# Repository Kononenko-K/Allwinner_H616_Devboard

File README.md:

# Allwinner_H616_Devboard
A minimalistic development board designed for the Cortex-A53 Allwinner H616 SoC using KiCad

## Overview
The goal of this project, based on the schematics of Orange Pi Zero 2 and Orange Pi Zero 3, was to create a minimalistic development board for the H616 SoC with a functional DDR3/LPDDR4 topology and power supply. This allows it to be used as a basic design that can be modified for specific applications.

## [Hardware](Hardware)
Both versions of the board are powered by the 64-bit 1.5GHz Quad-Core Cortex-A53 Allwinner H616 SoC, supporting either Allwinner H616 or its pin-to-pin compatible successor, Allwinner H618. The primary difference between these chips is the increased L2 cache size in the H618 model.
#### [DDR3 Version:](/Hardware/H616_DDR3)

The DDR3 variant features a compact design optimized for simplicity and ease of learning. Key components include:

- **Memory:** Up to 8 Gbit (1 GB) of BGA-96 16x DDR3 RAM
- **Power Management:** X-Powers AXP305 PMIC
- **Connectivity:** Micro SD slot, USB HS Host connector
- **Communication:** Integrated CP2102 USB-UART converter

#### [LPDDR4 Version:](/Hardware/H616_LPDDR4)

The LPDDR4 variant offers enhanced capabilities tailored for my specific application, while also remaining suitable for educational use:

- **Memory:** Up to 32 Gbit (4 GB) of BGA-200 32x LPDDR4 RAM
- **Power Management:** X-Powers AXP313A PMIC
- **Storage:** Integrated SD2.0 Flash Memory chip and MicroSD slot for flexible storage options
- **Auxiliary Processing:** Cortex-M4 STM32 microcontroller for additional processing tasks
- **Communication:** Integrated CP2102 USB-UART converter

To power the board via USB and connect external devices, a custom [USB board adapter](/Hardware/Debug_Adapter) is available.

### **Manufacturing specifications:**
- **Layers:** 4-layer design  
- **Trace/Space:** 3.5/3.5 mil  
- **Via Sizes:** 0.35/0.15 mm 
- **Prepreg:** 80u  

There are PDF documents available for both [DDR3](/Hardware/H616_DDR3/project.pdf) and [LPDDR4](/Hardware/H616_LPDDR4/project.pdf) versions.

## Software

### **Building from Mainline:**
#### Arm Trusted Firmware (TF-A):
- Source: [here](https://git.trustedfirmware.org/TF-A/trusted-firmware-a.git/)
```sh
make CROSS_COMPILE=aarch64-linux-gnu- PLAT=sun50i_h616 RESET_TO_BL31=1
```
After building, copy the `bl31.bin` file to the U-Boot sources directory.

#### U-Boot:
- Source: [here](https://github.com/u-boot/u-boot)
```sh
make ARCH=arm CROSS_COMPILE=aarch64-linux-gnu- orangepi_zero2_defconfig
make ARCH=arm CROSS_COMPILE=aarch64-linux-gnu- BL31=bl31.bin
```

#### Linux Kernel:
- Source: [www.kernel.org](http://www.kernel.org)
```sh
make ARCH=arm64 CROSS_COMPILE=aarch64-linux-gnu- defconfig
make ARCH=arm64 CROSS_COMPILE=aarch64-linux-gnu- Image modules dtbs
```

#### Rootfs:
Example sources for arm64 rootfs:
- [rcn-ee.com](https://rcn-ee.com/rootfs/eewiki/minfs)
- [Linaro.org](https://releases.linaro.org/openembedded/images/)

#### Preparing SD Card:
1. Create two partitions: a small fat32 for boot files and an ext4 for rootfs.
2. Write U-Boot to the card:
```sh
sudo dd if=/dev/zero of=/dev/mmcblk0 bs=1k count=1023 seek=1
sudo dd if=u-boot-sunxi-with-spl.bin of=/dev/mmcblk0 bs=1024 seek=8
```
3. Copy dtb and kernel image to the first partition, then unpack rootfs to the second.

If you prefer to load U-Boot into RAM and execute it directly over USB without using an SD card, you can use the `sunxi-fel` utility:  
   ```sh
   sudo sunxi-fel uboot u-boot-sunxi-with-spl.bin
   ```  
This method is useful for testing or when bypassing the SD card for some reason.

#### Booting from U-Boot:
Enter these commands in the U-Boot console:
```sh
setenv bootargs console=ttyS0,115200 root=/dev/mmcblk0p2 rw rootwait
setenv bootcmd "mmc rescan; fatload mmc 0:1 0x46000000 Image; fatload mmc 0:1 0x49000000 sun50i-h616-orangepi-zero2.dtb; booti 0x46000000 - 0x49000000"
```
Use a `boot.scr` file for automatic booting.

### **Using Buildroot:**
For LPDDR4 version:
```sh
make orangepi_zero3_defconfig
```
For DDR3 versions, modify the config:
```sh
BR2_LINUX_KERNEL_INTREE_DTS_NAME="allwinner/sun50i-h616-orangepi-zero2.dts"
BR2_TARGET_UBOOT_BOARD_DEFCONFIG="orangepi_zero2"
```
Download sources with `make source`, then build.

## License
- The **Hardware** in this project is licensed under the [CERN Open Hardware Licence Permissive (CERN OHL-P)](LICENSE).

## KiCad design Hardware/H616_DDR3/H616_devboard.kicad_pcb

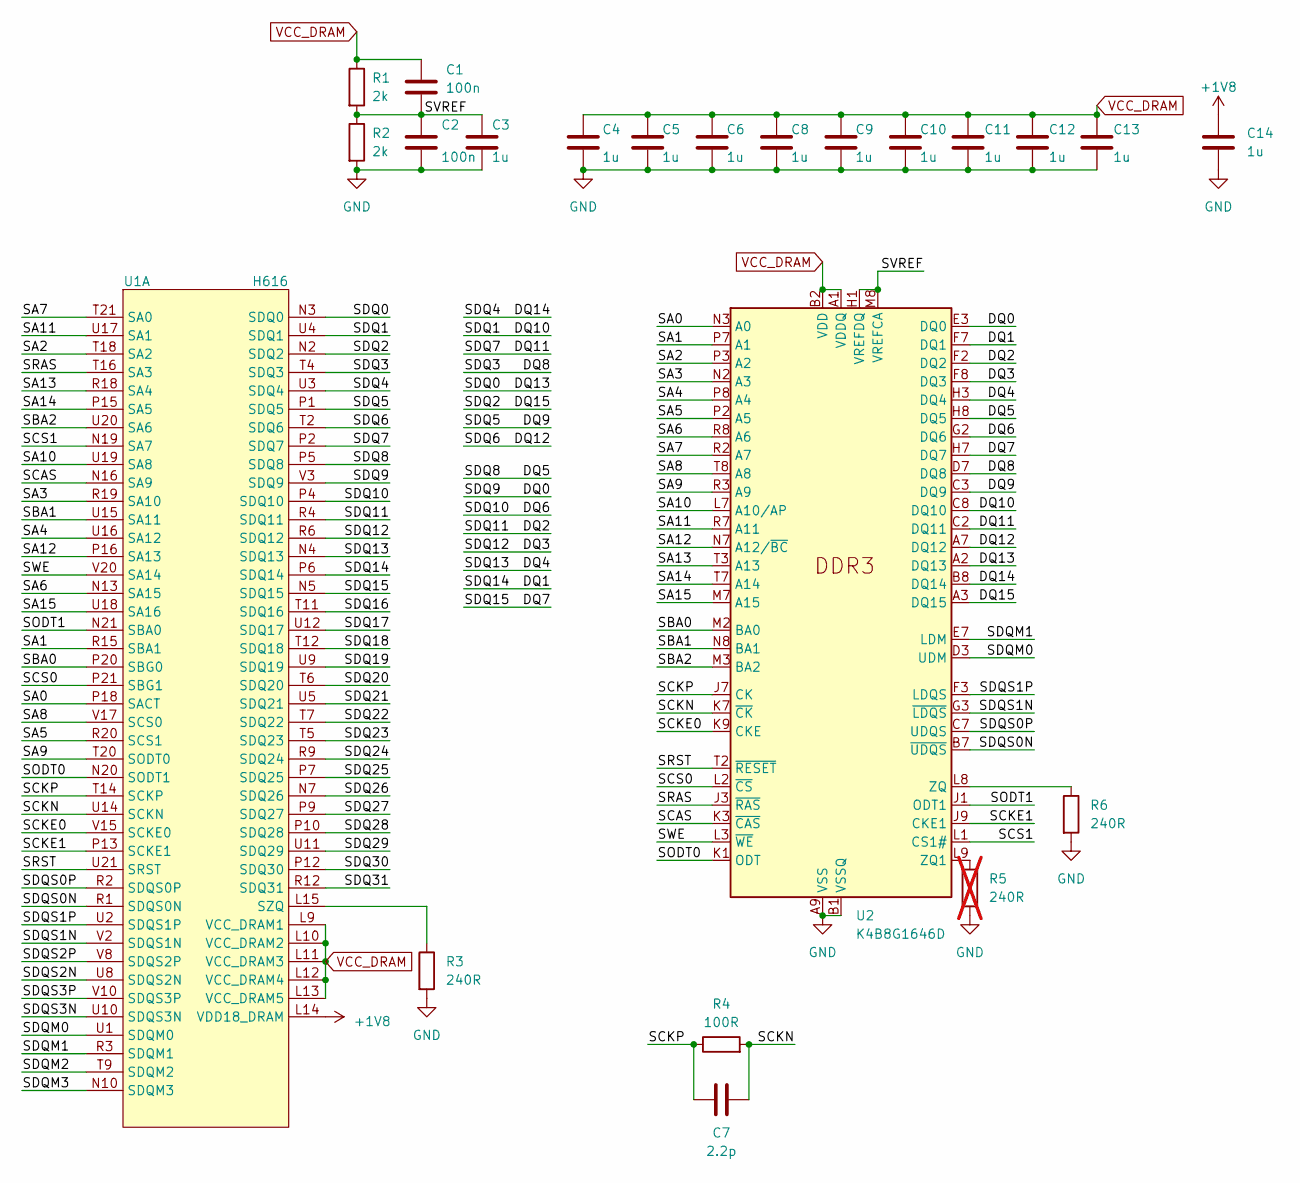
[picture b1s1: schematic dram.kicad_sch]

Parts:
C1, C2: 100n; C_0402_1005Metric_Pad0.74x0.62mm_HandSolder
C3, C4, C5, C6, C8, C9, C10, C11, C12, C13, C14: 1u; C_0402_1005Metric_Pad0.74x0.62mm_HandSolder
C7: 2.2p; C_0402_1005Metric_Pad0.74x0.62mm_HandSolder
R1, R2: 2k; R_0402_1005Metric_Pad0.72x0.64mm_HandSolder
R3, R6: 240R; R_0402_1005Metric_Pad0.72x0.64mm_HandSolder
R4: 100R; R_0402_1005Metric_Pad0.72x0.64mm_HandSolder
R5: 240R; R_0402_1005Metric_Pad0.72x0.64mm_HandSolder; not fitted
U1: H616; H616_TFBGA284
U2: K4B8G1646D; BGA-96_9.0x13.0mm_Layout2x3x16_P0.8mm

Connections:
+1V8: C14.1, U1.L14 (VDD18_DRAM); also elsewhere on the board
/DRAM/DQ0: U1.V3 (SDQ9), U2.E3 (DQ0)
/DRAM/DQ1: U1.P6 (SDQ14), U2.F7 (DQ1)
/DRAM/DQ2: U1.R4 (SDQ11), U2.F2 (DQ2)
/DRAM/DQ3: U1.R6 (SDQ12), U2.F8 (DQ3)
/DRAM/DQ4: U1.N4 (SDQ13), U2.H3 (DQ4)
/DRAM/DQ5: U1.P5 (SDQ8), U2.H8 (DQ5)
/DRAM/DQ6: U1.P4 (SDQ10), U2.G2 (DQ6)
/DRAM/DQ7: U1.N5 (SDQ15), U2.H7 (DQ7)
/DRAM/DQ8: U1.T4 (SDQ3), U2.D7 (DQ8)
/DRAM/DQ9: U1.P1 (SDQ5), U2.C3 (DQ9)
/DRAM/DQ10: U1.U4 (SDQ1), U2.C8 (DQ10)
/DRAM/DQ11: U1.P2 (SDQ7), U2.C2 (DQ11)
/DRAM/DQ12: U1.T2 (SDQ6), U2.A7 (DQ12)
/DRAM/DQ13: U1.N3 (SDQ0), U2.A2 (DQ13)
/DRAM/DQ14: U1.U3 (SDQ4), U2.B8 (DQ14)
/DRAM/DQ15: U1.N2 (SDQ2), U2.A3 (DQ15)
/DRAM/SA0: U1.P18 (SACT), U2.N3 (A0)
/DRAM/SA1: U1.R15 (SBA1), U2.P7 (A1)
/DRAM/SA2: U1.T18 (SA2), U2.P3 (A2)
/DRAM/SA3: U1.R19 (SA10), U2.N2 (A3)
/DRAM/SA4: U1.U16 (SA12), U2.P8 (A4)
/DRAM/SA5: U1.R20 (SCS1), U2.P2 (A5)
/DRAM/SA6: U1.N13 (SA15), U2.R8 (A6)
/DRAM/SA7: U1.T21 (SA0), U2.R2 (A7)
/DRAM/SA8: U1.V17 (SCS0), U2.T8 (A8)
/DRAM/SA9: U1.T20 (SODT0), U2.R3 (A9)
/DRAM/SA10: U1.U19 (SA8), U2.L7 (A10/AP)
/DRAM/SA11: U1.U17 (SA1), U2.R7 (A11)
/DRAM/SA12: U1.P16 (SA13), U2.N7 (A12/~BC)
/DRAM/SA13: U1.R18 (SA4), U2.T3 (A13)
/DRAM/SA14: U1.P15 (SA5), U2.T7 (A14)
/DRAM/SA15: U1.U18 (SA16), U2.M7 (A15)
/DRAM/SBA0: U1.P20 (SBG0), U2.M2 (BA0)
/DRAM/SBA1: U1.U15 (SA11), U2.N8 (BA1)
/DRAM/SBA2: U1.U20 (SA6), U2.M3 (BA2)
/DRAM/SCAS: U1.N16 (SA9), U2.K3 (~CAS)
/DRAM/SCKE0: U1.V15 (SCKE0), U2.K9 (CKE)
/DRAM/SCKE1: U1.P13 (SCKE1), U2.J9 (CKE1)
/DRAM/SCKN: C7.2, R4.2, U1.U14 (SCKN), U2.K7 (~CK)
/DRAM/SCKP: C7.1, R4.1, U1.T14 (SCKP), U2.J7 (CK)
/DRAM/SCS0: U1.P21 (SBG1), U2.L2 (~CS)
/DRAM/SCS1: U1.N19 (SA7), U2.L1 (CS1#)
/DRAM/SDQ16: U1.T11 (SDQ16)
/DRAM/SDQ17: U1.U12 (SDQ17)
/DRAM/SDQ18: U1.T12 (SDQ18)
/DRAM/SDQ19: U1.U9 (SDQ19)
/DRAM/SDQ20: U1.T6 (SDQ20)
/DRAM/SDQ21: U1.U5 (SDQ21)
/DRAM/SDQ22: U1.T7 (SDQ22)
/DRAM/SDQ23: U1.T5 (SDQ23)
/DRAM/SDQ24: U1.R9 (SDQ24)
/DRAM/SDQ25: U1.P7 (SDQ25)
/DRAM/SDQ26: U1.N7 (SDQ26)
/DRAM/SDQ27: U1.P9 (SDQ27)
/DRAM/SDQ28: U1.P10 (SDQ28)
/DRAM/SDQ29: U1.U11 (SDQ29)
/DRAM/SDQ30: U1.P12 (SDQ30)
/DRAM/SDQ31: U1.R12 (SDQ31)
/DRAM/SDQM0: U1.U1 (SDQM0), U2.D3 (UDM)
/DRAM/SDQM1: U1.R3 (SDQM1), U2.E7 (LDM)
/DRAM/SDQM2: U1.T9 (SDQM2)
/DRAM/SDQM3: U1.N10 (SDQM3)
/DRAM/SDQS0N: U1.R1 (SDQS0N), U2.B7 (~UDQS)
/DRAM/SDQS0P: U1.R2 (SDQS0P), U2.C7 (UDQS)
/DRAM/SDQS1N: U1.V2 (SDQS1N), U2.G3 (~LDQS)
/DRAM/SDQS1P: U1.U2 (SDQS1P), U2.F3 (LDQS)
/DRAM/SDQS2N: U1.U8 (SDQS2N)
/DRAM/SDQS2P: U1.V8 (SDQS2P)
/DRAM/SDQS3N: U1.U10 (SDQS3N)
/DRAM/SDQS3P: U1.V10 (SDQS3P)
/DRAM/SODT0: U1.N20 (SODT1), U2.K1 (ODT)
/DRAM/SODT1: U1.N21 (SBA0), U2.J1 (ODT1)
/DRAM/SRAS: U1.T16 (SA3), U2.J3 (~RAS)
/DRAM/SRST: U1.U21 (SRST), U2.T2 (~RESET)
/DRAM/SVREF: C1.2, C2.1, C3.1, R1.2, R2.1, U2.H1 (VREFDQ), U2.M8 (VREFCA)
/DRAM/SWE: U1.V20 (SA14), U2.L3 (~WE)
GND: C2.2, C3.2, C4.2, C5.2, C6.2, C8.2, C9.2, C10.2, C11.2, C12.2, C13.2, C14.2, R2.2, R3.2, R5.2, R6.2, U2.A9 (VSS), U2.B1 (VSSQ), U2.B3 (VSS), U2.B9 (VSSQ), U2.D1 (VSSQ), U2.D8 (VSSQ), U2.E1 (VSS), U2.E2 (VSSQ), U2.E8 (VSSQ), U2.F9 (VSSQ), U2.G1 (VSSQ), U2.G8 (VSS), U2.G9 (VSSQ), U2.J2 (VSS), U2.J8 (VSS), U2.M1 (VSS), U2.M9 (VSS), U2.P1 (VSS), U2.P9 (VSS), U2.T1 (VSS), U2.T9 (VSS); also elsewhere on the board
unnamed: R3.1, U1.L15 (SZQ)
unnamed: R5.1, U2.L9 (ZQ1)
unnamed: R6.1, U2.L8 (ZQ)
VCC_DRAM: C1.1, C4.1, C5.1, C6.1, C8.1, C9.1, C10.1, C11.1, C12.1, C13.1, R1.1, U1.L9 (VCC_DRAM1), U1.L10 (VCC_DRAM2), U1.L11 (VCC_DRAM3), U1.L12 (VCC_DRAM4), U1.L13 (VCC_DRAM5), U2.A1 (VDDQ), U2.A8 (VDDQ), U2.B2 (VDD), U2.C1 (VDDQ), U2.C9 (VDDQ), U2.D2 (VDDQ), U2.D9 (VDD), U2.E9 (VDDQ), U2.F1 (VDDQ), U2.G7 (VDD), U2.H2 (VDDQ), U2.H9 (VDDQ), U2.K2 (VDD), U2.K8 (VDD), U2.N1 (VDD), U2.N9 (VDD), U2.R1 (VDD), U2.R9 (VDD); also elsewhere on the board

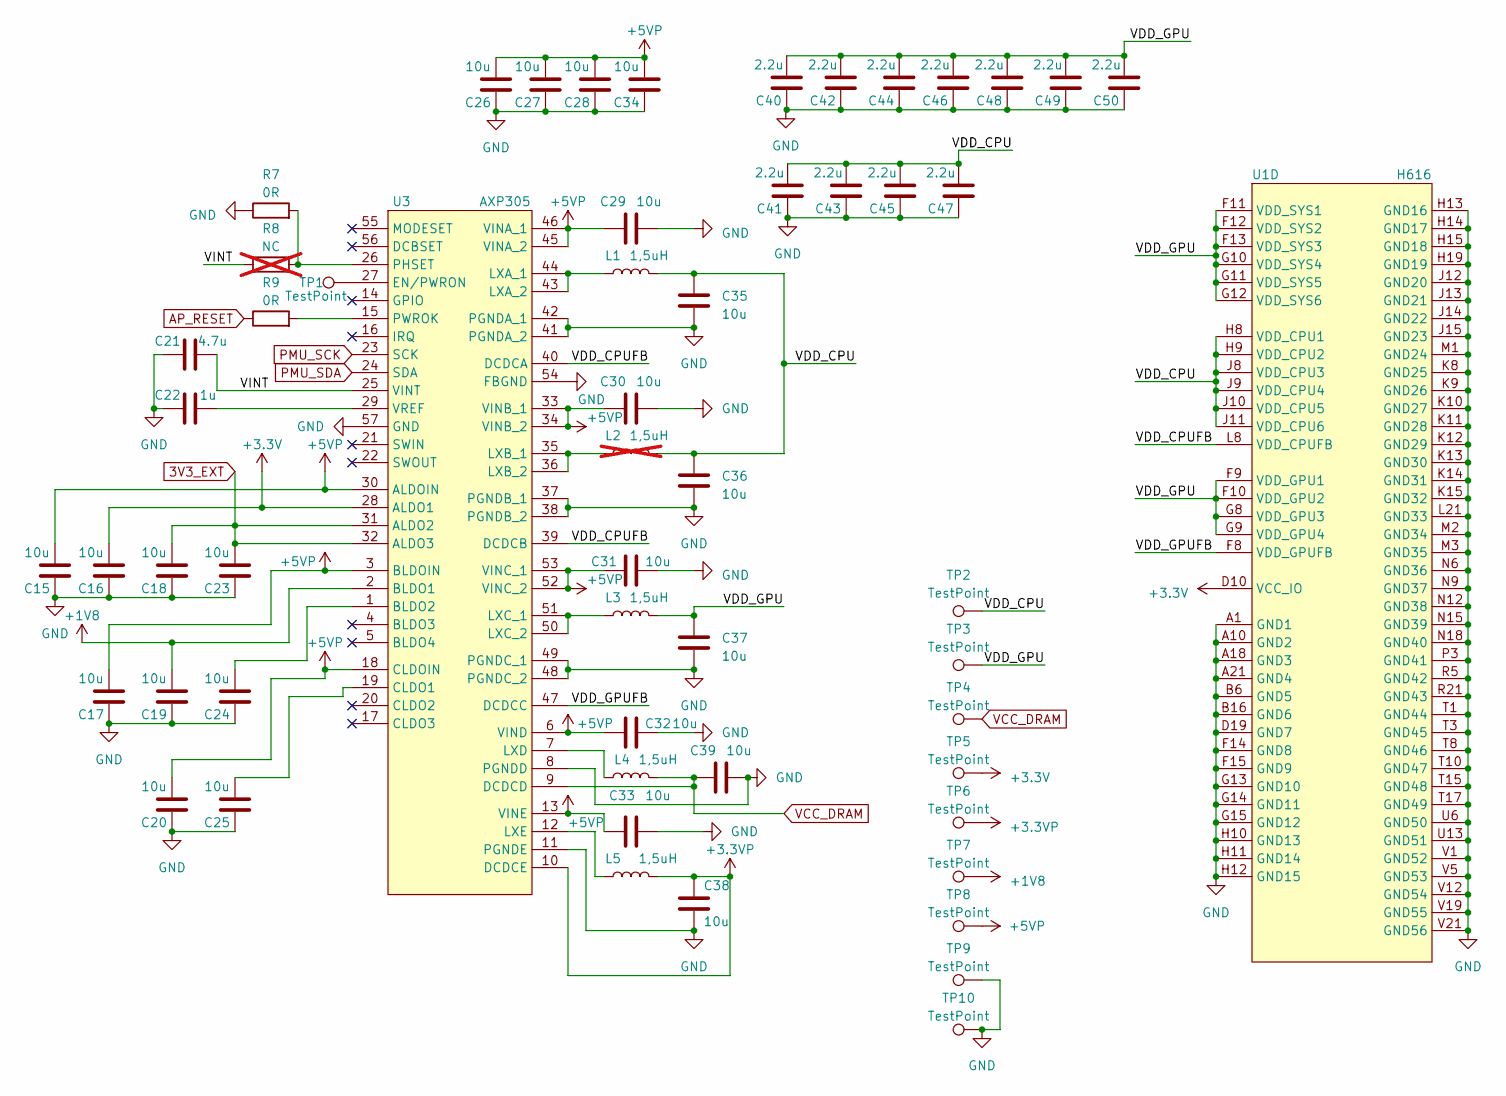
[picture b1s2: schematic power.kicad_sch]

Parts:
C15, C16, C17, C18, C19, C20, C23, C24, C25, C26, C27, C28, C29, C30, C31, C32, C33, C34, C35, C36, C37, C38, C39: 10u; C_0402_1005Metric_Pad0.74x0.62mm_HandSolder
C21: 4.7u; C_0402_1005Metric_Pad0.74x0.62mm_HandSolder
C22: 1u; C_0402_1005Metric_Pad0.74x0.62mm_HandSolder
C40, C41, C42, C43, C44, C45, C46, C47, C48, C49, C50: 2.2u; C_0402_1005Metric_Pad0.74x0.62mm_HandSolder
L1, L3, L4, L5: 1,5uH; L_Changjiang_FNR252010S
L2: 1,5uH; L_Changjiang_FNR252010S; not fitted
R7, R9: 0R; R_0402_1005Metric_Pad0.72x0.64mm_HandSolder
R8: NC; R_0402_1005Metric_Pad0.72x0.64mm_HandSolder; not fitted
TP1, TP2, TP3, TP4, TP5, TP6, TP7, TP8, TP9, TP10: TestPoint; TestPoint_THTPad_D1.0mm_Drill0.5mm
U1: H616; H616_TFBGA284
U3: AXP305; QFN-56-1EP_7x7mm_P0.4mm_EP4x4mm_ThermalVias

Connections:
3V3_EXT: C18.2, C23.2, U3.31 (ALDO2), U3.32 (ALDO3)
+1V8: C19.2, TP7.1, U3.2 (BLDO1); also elsewhere on the board
+3.3V: C16.2, TP5.1, U1.D10 (VCC_IO), U3.28 (ALDO1); also elsewhere on the board
+3.3VP: C38.2, L5.2, TP6.1, U3.10 (DCDCE)
+5VP: C15.2, C17.2, C20.2, C26.2, C27.2, C28.2, C29.1, C30.1, C31.1, C32.1, C33.1, C34.2, TP8.1, U3.3 (BLDOIN), U3.6 (VIND), U3.13 (VINE), U3.18 (CLDOIN), U3.30 (ALDOIN), U3.33 (VINB_1), U3.34 (VINB_2), U3.45 (VINA_2), U3.46 (VINA_1), U3.52 (VINC_2), U3.53 (VINC_1); also elsewhere on the board
/POWER/VDD_CPU: C35.1, C36.1, C41.2, C43.2, C45.2, C47.2, L1.2, L2.2, TP2.1, U1.H8 (VDD_CPU1), U1.H9 (VDD_CPU2), U1.J8 (VDD_CPU3), U1.J9 (VDD_CPU4), U1.J10 (VDD_CPU5), U1.J11 (VDD_CPU6)
/POWER/VDD_CPUFB: U1.L8 (VDD_CPUFB), U3.39 (DCDCB), U3.40 (DCDCA)
/POWER/VDD_GPU: C37.1, C40.2, C42.2, C44.2, C46.2, C48.2, C49.2, C50.2, L3.2, TP3.1, U1.F9 (VDD_GPU1), U1.F10 (VDD_GPU2), U1.F11 (VDD_SYS1), U1.F12 (VDD_SYS2), U1.F13 (VDD_SYS3), U1.G8 (VDD_GPU3), U1.G9 (VDD_GPU4), U1.G10 (VDD_SYS4), U1.G11 (VDD_SYS5), U1.G12 (VDD_SYS6)
/POWER/VDD_GPUFB: U1.F8 (VDD_GPUFB), U3.47 (DCDCC)
/POWER/VINT: C21.2, R8.1, U3.25 (VINT)
AP_RESET: R9.1; also elsewhere on the board
GND: C15.1, C16.1, C17.1, C18.1, C19.1, C20.1, C21.1, C22.1, C23.1, C24.1, C25.1, C26.1, C27.1, C28.1, C29.2, C30.2, C31.2, C32.2, C33.2, C34.1, C35.2, C36.2, C37.2, C38.1, C39.2, C40.1, C41.1, C42.1, C43.1, C44.1, C45.1, C46.1, C47.1, C48.1, C49.1, C50.1, R7.1, TP9.1, TP10.1, U1.A1 (GND1), U1.A10 (GND2), U1.A18 (GND3), U1.A21 (GND4), U1.B6 (GND5), U1.B16 (GND6), U1.D19 (GND7), U1.F14 (GND8), U1.F15 (GND9), U1.G13 (GND10), U1.G14 (GND11), U1.G15 (GND12), U1.H10 (GND13), U1.H11 (GND14), U1.H12 (GND15), U1.H13 (GND16), U1.H14 (GND17), U1.H15 (GND18), U1.H19 (GND19), U1.J12 (GND20), U1.J13 (GND21), U1.J14 (GND22), U1.J15 (GND23), U1.K8 (GND25), U1.K9 (GND26), U1.K10 (GND27), U1.K11 (GND28), U1.K12 (GND29), U1.K13 (GND30), U1.K14 (GND31), U1.K15 (GND32), U1.L21 (GND33), U1.M1 (GND24), U1.M2 (GND34), U1.M3 (GND35), U1.N6 (GND36), U1.N9 (GND37), U1.N12 (GND38), U1.N15 (GND39), U1.N18 (GND40), U1.P3 (GND41), U1.R5 (GND42), U1.R21 (GND43), U1.T1 (GND44), U1.T3 (GND45), U1.T8 (GND46), U1.T10 (GND47), U1.T15 (GND48), U1.T17 (GND49), U1.U6 (GND50), U1.U13 (GND51), U1.V1 (GND52), U1.V5 (GND53), U1.V12 (GND54), U1.V19 (GND55), U1.V21 (GND56), U3.8 (PGNDD), U3.11 (PGNDE), U3.37 (PGNDB_1), U3.38 (PGNDB_2), U3.41 (PGNDA_2), U3.42 (PGNDA_1), U3.48 (PGNDC_2), U3.49 (PGNDC_1), U3.54 (FBGND), U3.57 (GND); also elsewhere on the board
unnamed: C24.2, U3.1 (BLDO2)
unnamed: C25.2, U3.19 (CLDO1)
unnamed: TP1.1, U3.27 (EN/PWRON)
unnamed: L1.1, U3.43 (LXA_2), U3.44 (LXA_1)
unnamed: L2.1, U3.35 (LXB_1), U3.36 (LXB_2)
unnamed: L3.1, U3.50 (LXC_2), U3.51 (LXC_1)
unnamed: L4.1, U3.7 (LXD)
unnamed: L5.1, U3.12 (LXE)
unnamed: R7.2, R8.2, U3.26 (PHSET)
unnamed: R9.2, U3.15 (PWROK)
unnamed: C22.2, U3.29 (VREF)
PMU_SCK: U3.23 (SCK); also elsewhere on the board
PMU_SDA: U3.24 (SDA); also elsewhere on the board
VCC_DRAM: C39.1, L4.2, TP4.1, U3.9 (DCDCD); also elsewhere on the board

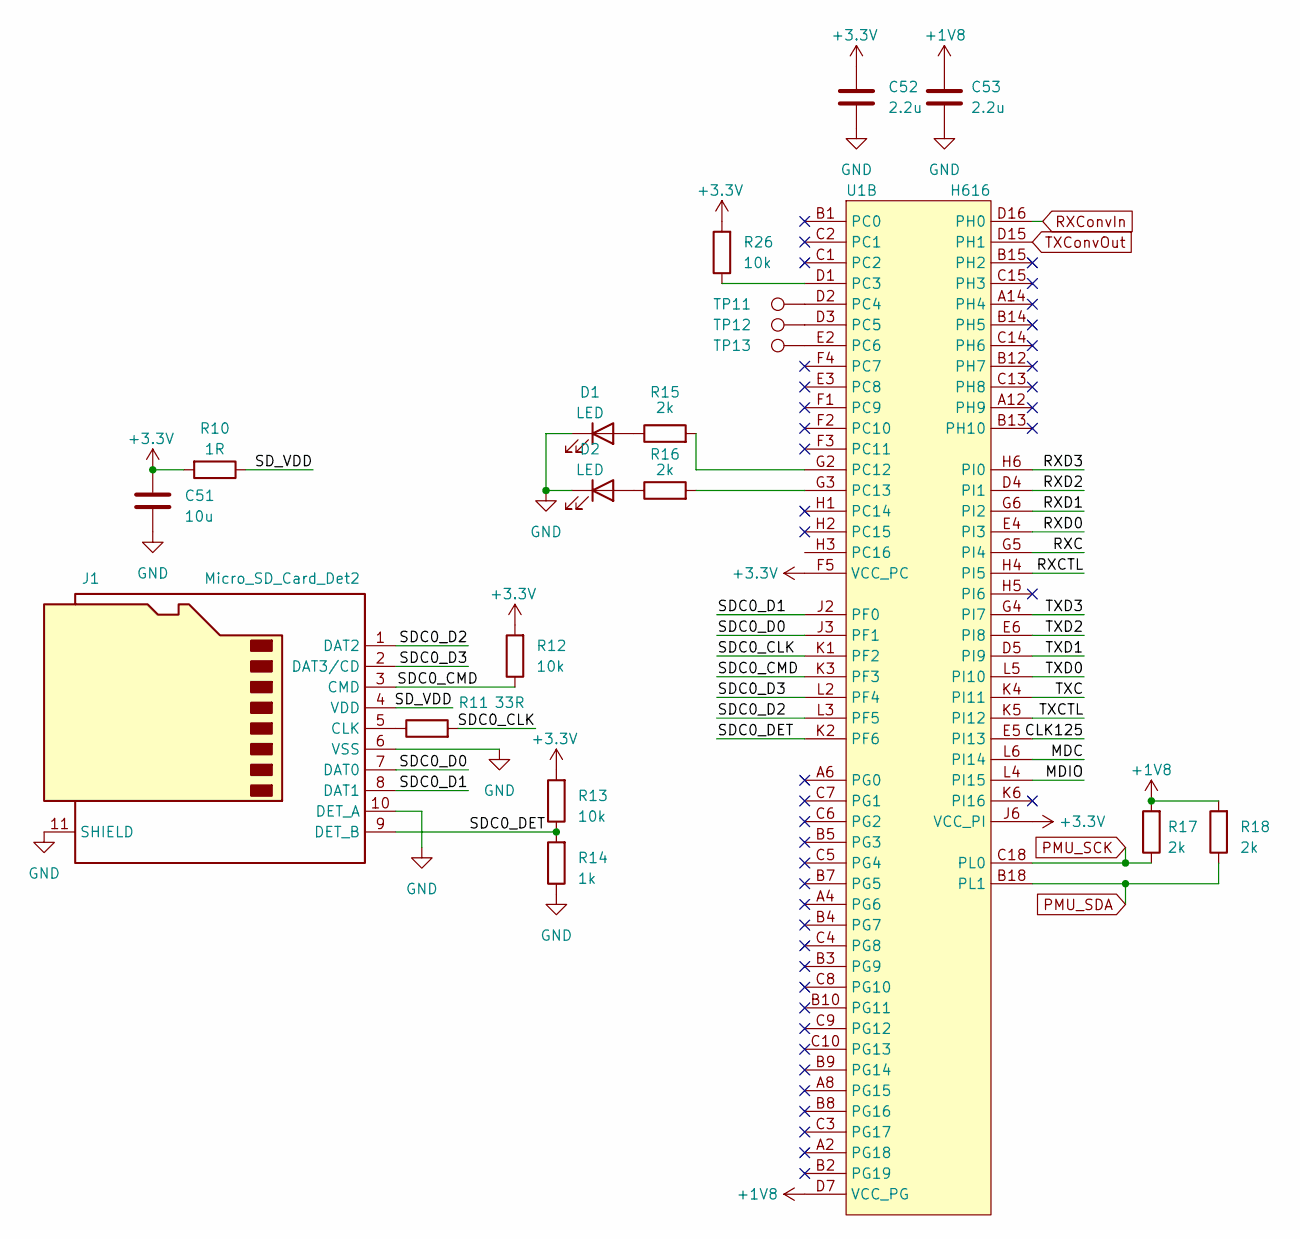
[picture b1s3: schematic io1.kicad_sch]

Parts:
C51: 10u; C_0402_1005Metric_Pad0.74x0.62mm_HandSolder
C52, C53: 2.2u; C_0402_1005Metric_Pad0.74x0.62mm_HandSolder
D1, D2: LED; LED_0603_1608Metric_Pad1.05x0.95mm_HandSolder
J1: Micro_SD_Card_Det2; microSD_HC_Hirose_DM3AT-SF-PEJM5
R10: 1R; R_0402_1005Metric_Pad0.72x0.64mm_HandSolder
R11: 33R; R_0402_1005Metric_Pad0.72x0.64mm_HandSolder
R12, R13, R26: 10k; R_0402_1005Metric_Pad0.72x0.64mm_HandSolder
R14: 1k; R_0402_1005Metric_Pad0.72x0.64mm_HandSolder
R15, R16, R17, R18: 2k; R_0402_1005Metric_Pad0.72x0.64mm_HandSolder
TP11, TP12, TP13: TestPoint; TestPoint_THTPad_D1.0mm_Drill0.5mm
U1: H616; H616_TFBGA284

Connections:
+1V8: C53.1, R17.2, R18.2, U1.D7 (VCC_PG); also elsewhere on the board
+3.3V: C51.1, C52.1, R10.2, R12.2, R13.2, R26.2, U1.F5 (VCC_PC), U1.J6 (VCC_PI); also elsewhere on the board
/IO1/CLK125: U1.E5 (PI13)
/IO1/MDC: U1.L6 (PI14)
/IO1/MDIO: U1.L4 (PI15)
/IO1/RXC: U1.G5 (PI4)
/IO1/RXCTL: U1.H4 (PI5)
/IO1/RXD0: U1.E4 (PI3)
/IO1/RXD1: U1.G6 (PI2)
/IO1/RXD2: U1.D4 (PI1)
/IO1/RXD3: U1.H6 (PI0)
/IO1/SDC0_CLK: R11.2, U1.K1 (PF2)
/IO1/SDC0_CMD: J1.3 (CMD), R12.1, U1.K3 (PF3)
/IO1/SDC0_D0: J1.7 (DAT0), U1.J3 (PF1)
/IO1/SDC0_D1: J1.8 (DAT1), U1.J2 (PF0)
/IO1/SDC0_D2: J1.1 (DAT2), U1.L3 (PF5)
/IO1/SDC0_D3: J1.2 (DAT3/CD), U1.L2 (PF4)
/IO1/SDC0_DET: J1.9 (DET_B), R13.1, R14.2, U1.K2 (PF6)
/IO1/SD_VDD: J1.4 (VDD), R10.1
/IO1/TXC: U1.K4 (PI11)
/IO1/TXCTL: U1.K5 (PI12)
/IO1/TXD0: U1.L5 (PI10)
/IO1/TXD1: U1.D5 (PI9)
/IO1/TXD2: U1.E6 (PI8)
/IO1/TXD3: U1.G4 (PI7)
GND: C51.2, C52.2, C53.2, D1.1 (K), D2.1 (K), J1.6 (VSS), J1.10 (DET_A), J1.11 (SHIELD), R14.1; also elsewhere on the board
unnamed: D1.2 (A), R15.1
unnamed: D2.2 (A), R16.1
unnamed: J1.5 (CLK), R11.1
unnamed: R26.1, U1.D1 (PC3)
unnamed: TP11.1, U1.D2 (PC4)
unnamed: TP12.1, U1.D3 (PC5)
unnamed: TP13.1, U1.E2 (PC6)
unnamed: R15.2, U1.G2 (PC12)
unnamed: R16.2, U1.G3 (PC13)
PMU_SCK: R17.1, U1.C18 (PL0); also elsewhere on the board
PMU_SDA: R18.1, U1.B18 (PL1); also elsewhere on the board
RXConvIn: U1.D16 (PH0); also elsewhere on the board
TXConvOut: U1.D15 (PH1); also elsewhere on the board

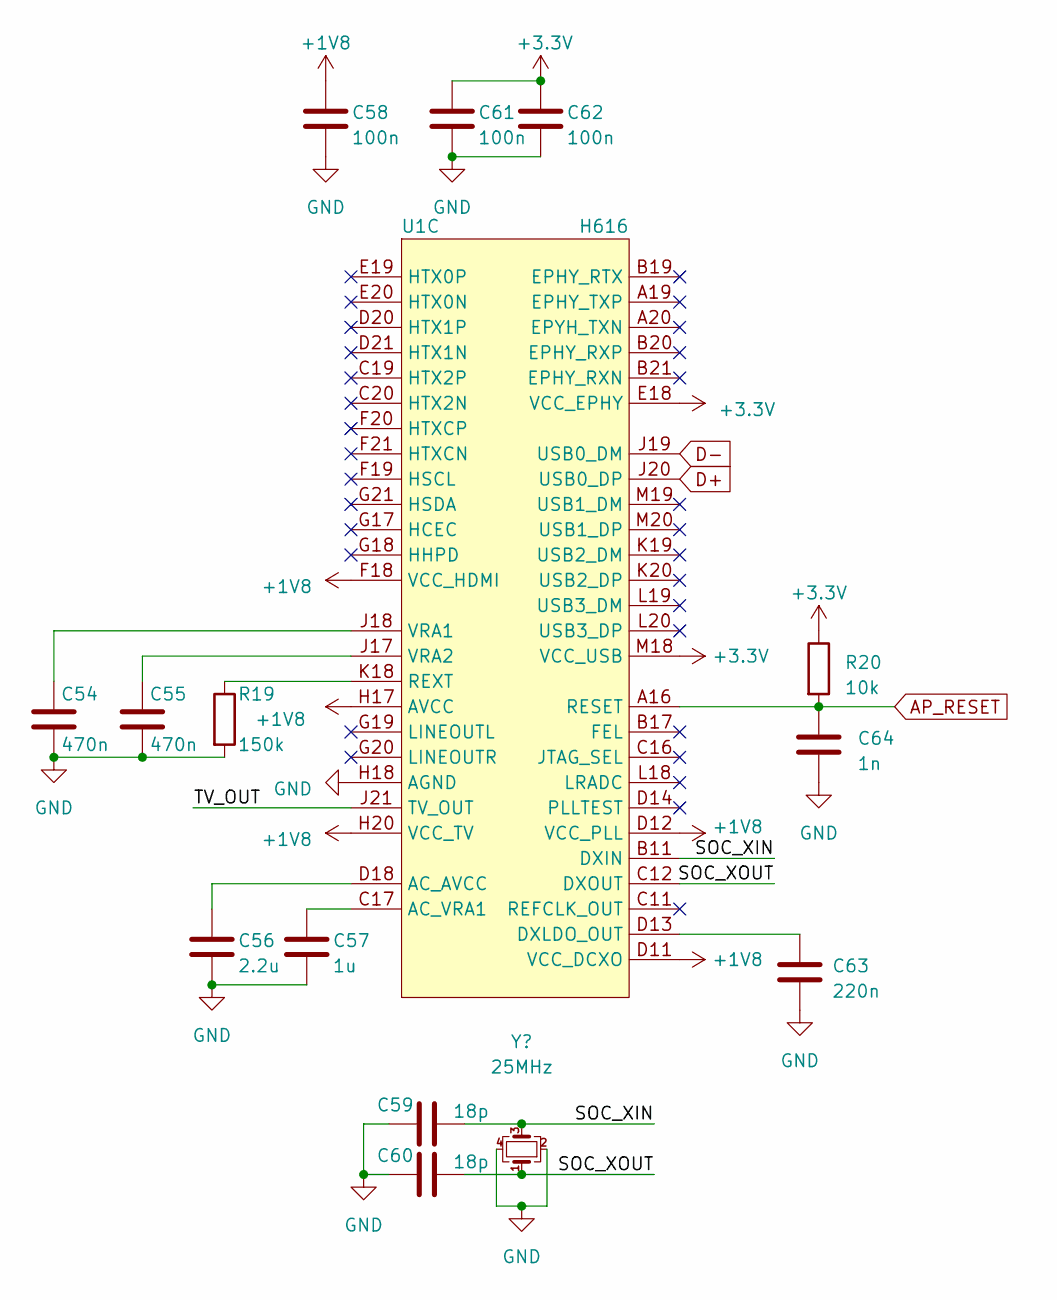
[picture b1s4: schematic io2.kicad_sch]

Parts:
C54, C55: 470n; C_0402_1005Metric_Pad0.74x0.62mm_HandSolder
C56: 2.2u; C_0402_1005Metric_Pad0.74x0.62mm_HandSolder
C57: 1u; C_0402_1005Metric_Pad0.74x0.62mm_HandSolder
C58, C61, C62: 100n; C_0402_1005Metric_Pad0.74x0.62mm_HandSolder
C59, C60: 18p; C_0402_1005Metric_Pad0.74x0.62mm_HandSolder
C63: 220n; C_0402_1005Metric_Pad0.74x0.62mm_HandSolder
C64: 1n; C_0402_1005Metric_Pad0.74x0.62mm_HandSolder
R19: 150k; R_0402_1005Metric_Pad0.72x0.64mm_HandSolder
R20: 10k; R_0402_1005Metric_Pad0.72x0.64mm_HandSolder
U1: H616; H616_TFBGA284
Y1: 25MHz; Crystal_SMD_2520-4Pin_2.5x2.0mm

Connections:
+1V8: C58.1, U1.D11 (VCC_DCXO), U1.D12 (VCC_PLL), U1.F18 (VCC_HDMI), U1.H17 (AVCC), U1.H20 (VCC_TV); also elsewhere on the board
+3.3V: C61.1, C62.1, R20.1, U1.E18 (VCC_EPHY), U1.M18 (VCC_USB); also elsewhere on the board
/IO2/SOC_XIN: C59.2, U1.B11 (DXIN), Y1.3
/IO2/SOC_XOUT: C60.2, U1.C12 (DXOUT), Y1.1
/IO2/TV_OUT: U1.J21 (TV_OUT)
AP_RESET: C64.1, R20.2, U1.A16 (RESET); also elsewhere on the board
D+: U1.J20 (USB0_DP); also elsewhere on the board
D-: U1.J19 (USB0_DM); also elsewhere on the board
GND: C54.2, C55.2, C56.2, C57.2, C58.2, C59.1, C60.1, C61.2, C62.2, C63.2, C64.2, R19.2, U1.H18 (AGND), Y1.2, Y1.4; also elsewhere on the board
unnamed: C56.1, U1.D18 (AC_AVCC)
unnamed: C57.1, U1.C17 (AC_VRA1)
unnamed: C63.1, U1.D13 (DXLDO_OUT)
unnamed: R19.1, U1.K18 (REXT)
unnamed: C54.1, U1.J18 (VRA1)
unnamed: C55.1, U1.J17 (VRA2)

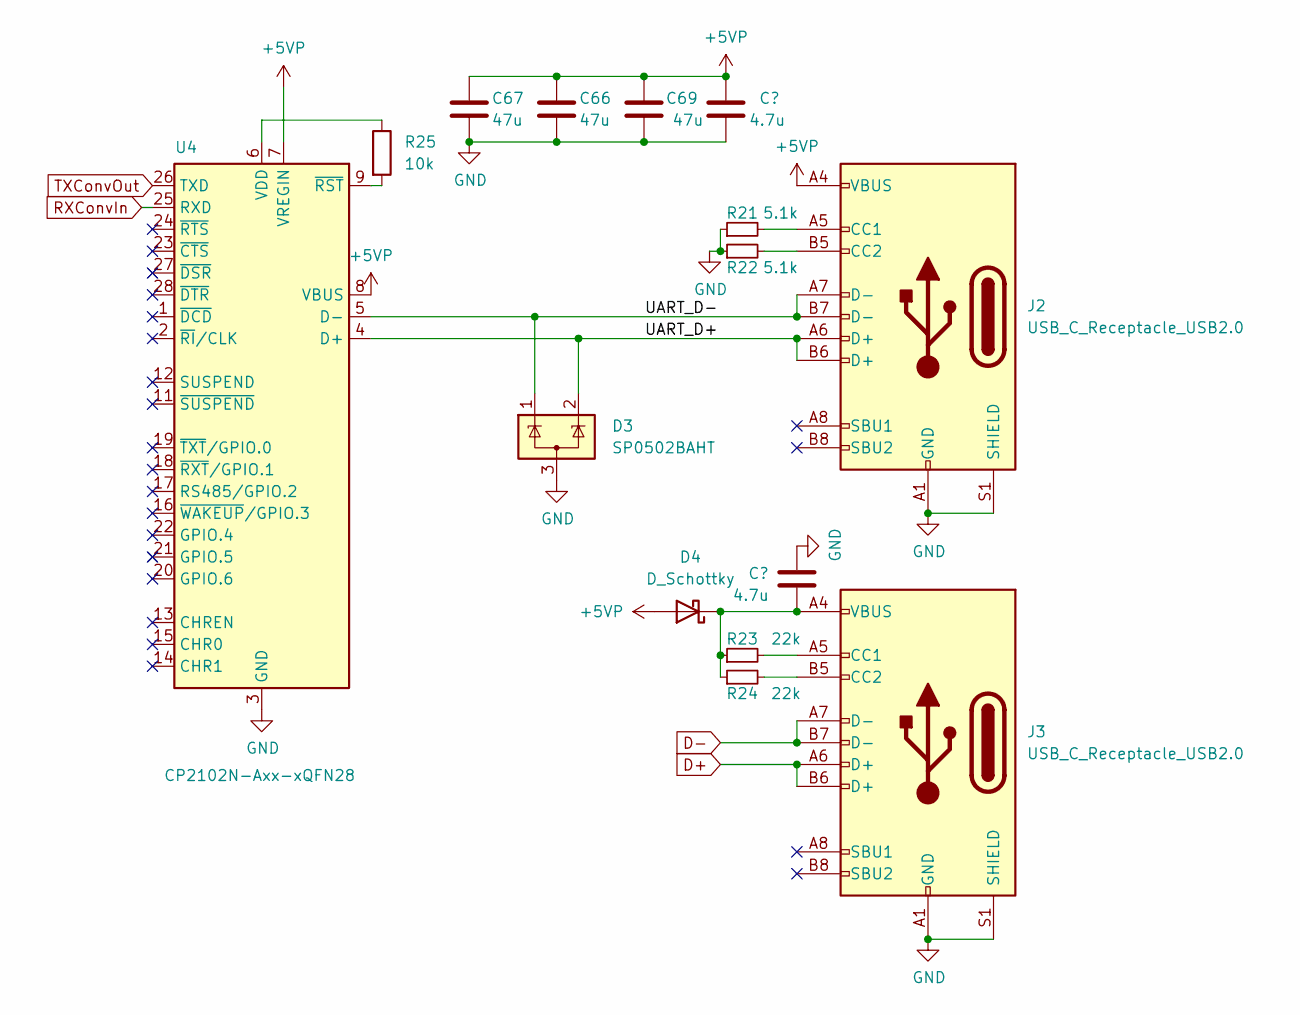
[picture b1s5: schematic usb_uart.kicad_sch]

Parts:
C65, C68: 4.7u; C_0402_1005Metric_Pad0.74x0.62mm_HandSolder
C66, C67, C69: 47u; C_1206_3216Metric_Pad1.33x1.80mm_HandSolder
D3: SP0502BAHT; SOT-23
D4: D_Schottky; D_SOD-323_HandSoldering
J2, J3: USB_C_Receptacle_USB2.0; USB_C_Receptacle_Palconn_UTC16-G
R21, R22: 5.1k; R_0402_1005Metric_Pad0.72x0.64mm_HandSolder
R23, R24: 22k; R_0402_1005Metric_Pad0.72x0.64mm_HandSolder
R25: 10k; R_0402_1005Metric_Pad0.72x0.64mm_HandSolder
U4: CP2102N-Axx-xQFN28; QFN-28-1EP_5x5mm_P0.5mm_EP3.35x3.35mm

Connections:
+5VP: C66.1, C67.1, C68.1, C69.1, D4.2 (A), J2.A4 (VBUS), J2.A9 (VBUS), J2.B4 (VBUS), J2.B9 (VBUS), U4.7 (VREGIN), U4.8 (VBUS); also elsewhere on the board
/USB-UART/UART_D+: D3.2 (K), J2.A6 (D+), J2.B6 (D+), U4.4 (D+)
/USB-UART/UART_D-: D3.1 (K), J2.A7 (D-), J2.B7 (D-), U4.5 (D-)
D+: J3.A6 (D+), J3.B6 (D+); also elsewhere on the board
D-: J3.A7 (D-), J3.B7 (D-); also elsewhere on the board
GND: C65.1, C66.2, C67.2, C68.2, C69.2, D3.3 (A), J2.A1 (GND), J2.A12 (GND), J2.B1 (GND), J2.B12 (GND), J2.S1 (SHIELD), J3.A1 (GND), J3.A12 (GND), J3.B1 (GND), J3.B12 (GND), J3.S1 (SHIELD), R21.1, R22.1, U4.3 (GND), U4.29 (GND); also elsewhere on the board
unnamed: C65.2, D4.1 (K), J3.A4 (VBUS), J3.A9 (VBUS), J3.B4 (VBUS), J3.B9 (VBUS), R23.1, R24.1
unnamed: J2.A5 (CC1), R21.2
unnamed: J2.B5 (CC2), R22.2
unnamed: J3.A5 (CC1), R23.2
unnamed: J3.B5 (CC2), R24.2
unnamed: R25.1, U4.6 (VDD)
unnamed: R25.2, U4.9 (~RST)
RXConvIn: U4.25 (RXD); also elsewhere on the board
TXConvOut: U4.26 (TXD); also elsewhere on the board

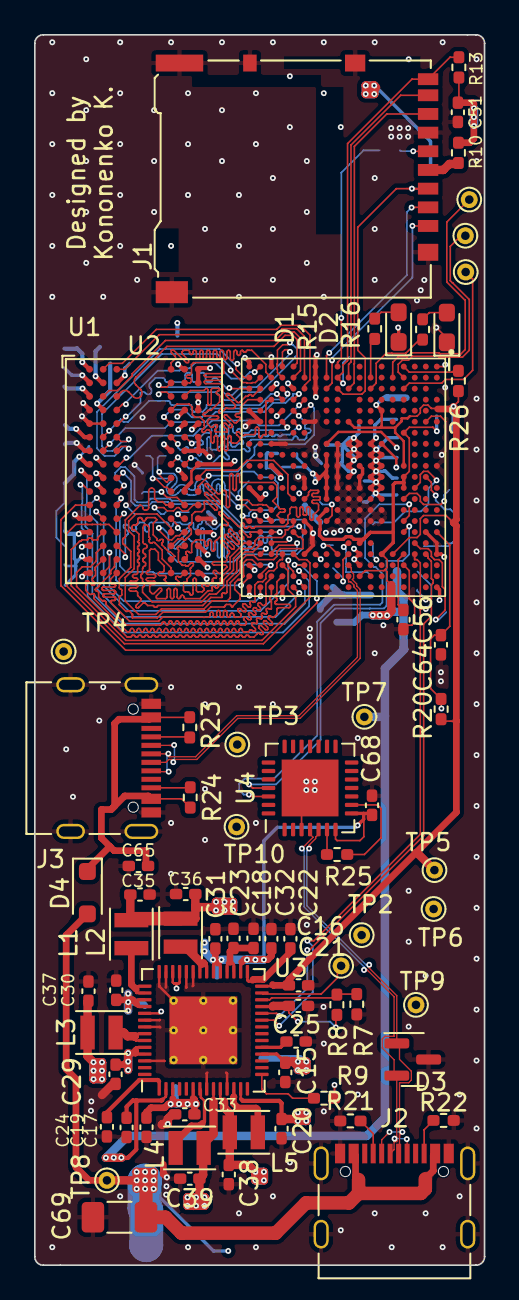
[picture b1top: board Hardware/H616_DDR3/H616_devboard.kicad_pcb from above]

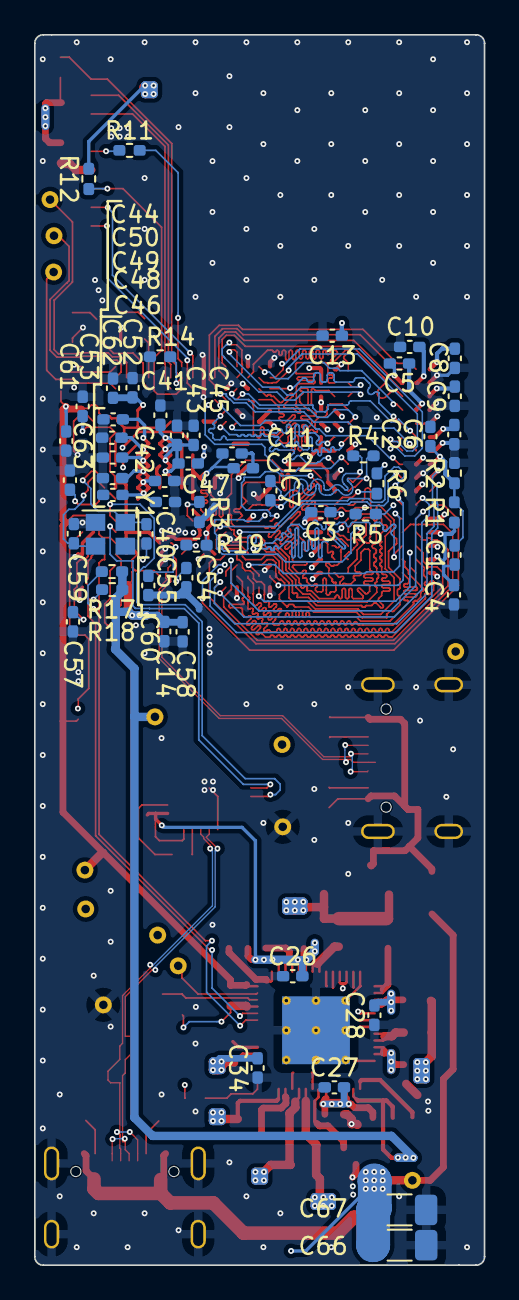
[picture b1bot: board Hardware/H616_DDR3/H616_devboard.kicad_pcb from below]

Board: 4 copper layers, 26.5 x 72.5 mm, 125 parts (55 on the bottom side), 121 nets.

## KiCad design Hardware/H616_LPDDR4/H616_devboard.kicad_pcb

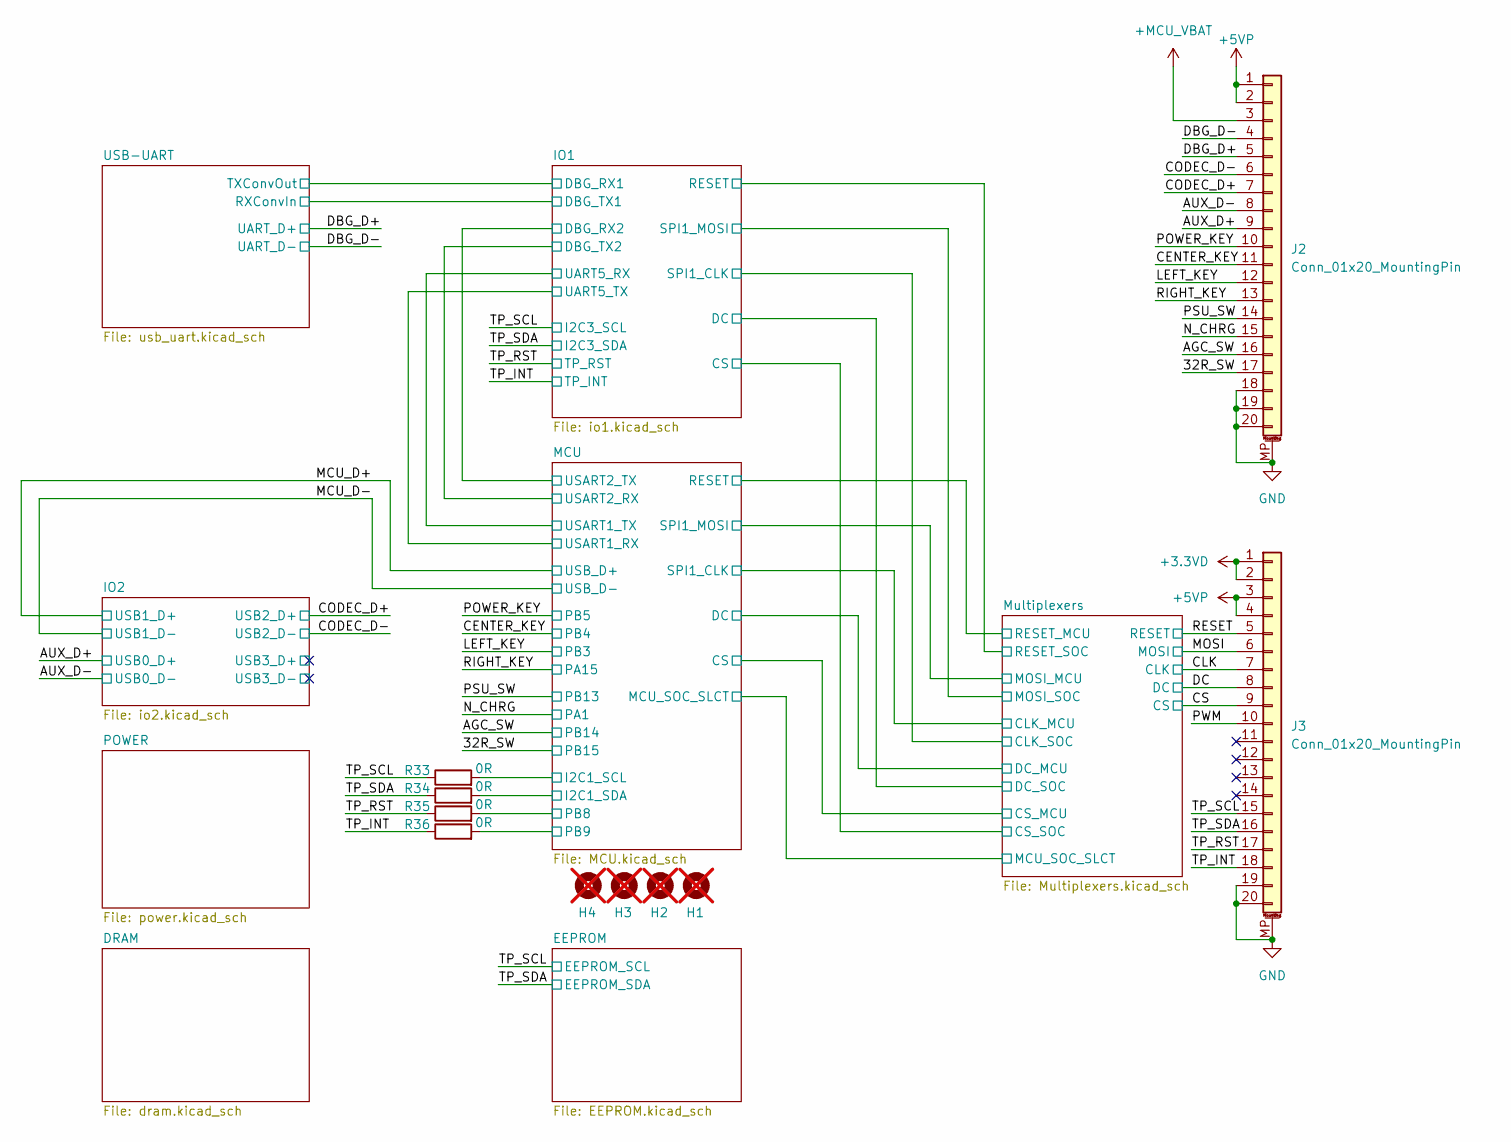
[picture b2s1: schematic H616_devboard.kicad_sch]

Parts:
H1, H2, H3, H4: MountingHole; MountingHole_3.2mm_M3_DIN965; not fitted
J2, J3: Conn_01x20_MountingPin; TE_2-84952-0_1x20-1MP_P1.0mm_Horizontal; Part Number XW10202-20R-00
R33, R34, R35, R36: 0R; R_0402_1005Metric_Pad0.72x0.64mm_HandSolder; Part Number RC0402FR-070RL

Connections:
+3.3VD: J3.1, J3.2; also elsewhere on the board
+5VP: J2.1, J2.2, J3.3, J3.4; also elsewhere on the board
+MCU_VBAT: J2.3; also elsewhere on the board
/32R_SW: J2.17; also elsewhere on the board
/AGC_SW: J2.16; also elsewhere on the board
/AUX_D+: J2.9; also elsewhere on the board
/AUX_D-: J2.8; also elsewhere on the board
/CENTER_KEY: J2.11; also elsewhere on the board
/CLK: J3.7; also elsewhere on the board
/CODEC_D+: J2.7; also elsewhere on the board
/CODEC_D-: J2.6; also elsewhere on the board
/CS: J3.9; also elsewhere on the board
/DBG_D+: J2.5; also elsewhere on the board
/DBG_D-: J2.4; also elsewhere on the board
/DC: J3.8; also elsewhere on the board
/LEFT_KEY: J2.12; also elsewhere on the board
/MCU/I2C1_SCL: R33.2; also elsewhere on the board
/MCU/I2C1_SDA: R34.2; also elsewhere on the board
/MCU/PB8: R35.2; also elsewhere on the board
/MCU/PB9: R36.2; also elsewhere on the board
/MOSI: J3.6; also elsewhere on the board
/N_CHRG: J2.15; also elsewhere on the board
/POWER_KEY: J2.10; also elsewhere on the board
/PSU_SW: J2.14; also elsewhere on the board
/PWM: J3.10
/RESET: J3.5; also elsewhere on the board
/RIGHT_KEY: J2.13; also elsewhere on the board
/TP_INT: J3.18, R36.1; also elsewhere on the board
/TP_RST: J3.17, R35.1; also elsewhere on the board
/TP_SCL: J3.15, R33.1; also elsewhere on the board
/TP_SDA: J3.16, R34.1; also elsewhere on the board
GND: J2.18, J2.19, J2.20, J2.MP (MountPin), J3.19, J3.20, J3.MP (MountPin); also elsewhere on the board
